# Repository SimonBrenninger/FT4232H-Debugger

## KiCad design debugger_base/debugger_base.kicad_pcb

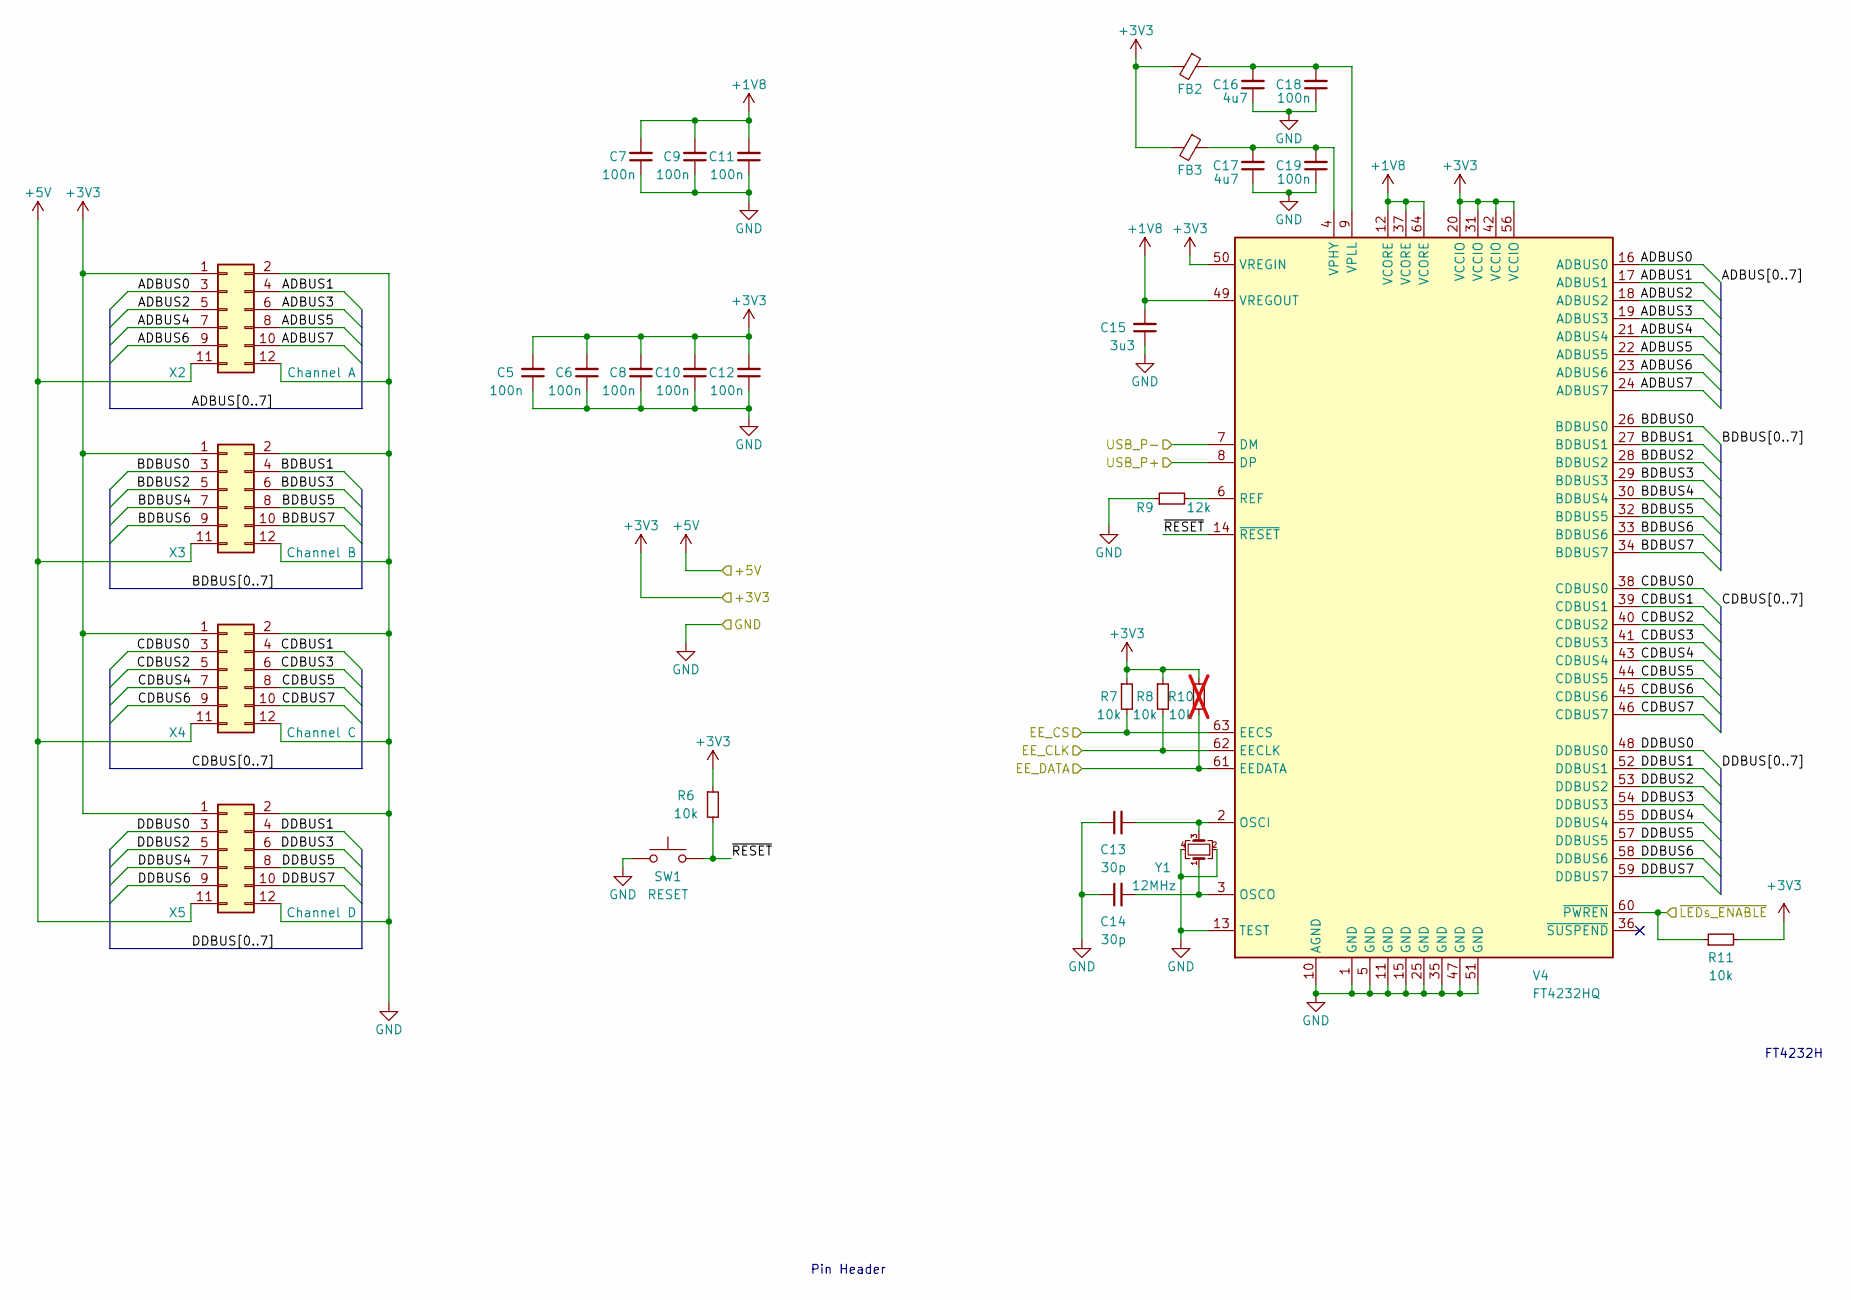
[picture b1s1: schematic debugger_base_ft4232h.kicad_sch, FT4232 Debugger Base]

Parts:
C5, C6, C7, C8, C9, C10, C11, C12, C18, C19: 100n; C_0402_1005Metric
C13, C14: 30p; C_0402_1005Metric
C15: 3u3; C_0402_1005Metric
C16, C17: 4u7; C_0402_1005Metric
FB2, FB3: FerriteBead_Small; L_0603_1608Metric
R6, R7, R8, R11: 10k; R_0402_1005Metric
R9: 12k; R_0402_1005Metric
R10: 10k; R_0402_1005Metric; not fitted
SW1: RESET; SW_SPST_EVQP2
V4: FT4232HQ; QFN-64-1EP_9x9mm_P0.5mm_EP4.35x4.35mm
X2: Channel A; header_female_02x06_613012243121
X3: Channel B; header_female_02x06_613012243121
X4: Channel C; header_female_02x06_613012243121
X5: Channel D; header_female_02x06_613012243121
Y1: 12MHz; Crystal_SMD_3225-4Pin_3.2x2.5mm

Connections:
+1V8: C7.2, C9.2, C11.2, C15.2, V4.12 (VCORE), V4.37 (VCORE), V4.49 (VREGOUT), V4.64 (VCORE)
+3V3: C5.2, C6.2, C8.2, C10.2, C12.2, FB2.2, FB3.2, R6.1, R7.1, R8.1, R10.1, R11.2, V4.20 (VCCIO), V4.31 (VCCIO), V4.42 (VCCIO), V4.50 (VREGIN), V4.56 (VCCIO), X2.1, X3.1, X4.1, X5.1; also elsewhere on the board
+5V: X2.11, X3.11, X4.11, X5.11; also elsewhere on the board
/FT4232H/ADBUS0: V4.16 (ADBUS0), X2.3
/FT4232H/ADBUS1: V4.17 (ADBUS1), X2.4
/FT4232H/ADBUS2: V4.18 (ADBUS2), X2.5
/FT4232H/ADBUS3: V4.19 (ADBUS3), X2.6
/FT4232H/ADBUS4: V4.21 (ADBUS4), X2.7
/FT4232H/ADBUS5: V4.22 (ADBUS5), X2.8
/FT4232H/ADBUS6: V4.23 (ADBUS6), X2.9
/FT4232H/ADBUS7: V4.24 (ADBUS7), X2.10
/FT4232H/BDBUS0: V4.26 (BDBUS0), X3.3
/FT4232H/BDBUS1: V4.27 (BDBUS1), X3.4
/FT4232H/BDBUS2: V4.28 (BDBUS2), X3.5
/FT4232H/BDBUS3: V4.29 (BDBUS3), X3.6
/FT4232H/BDBUS4: V4.30 (BDBUS4), X3.7
/FT4232H/BDBUS5: V4.32 (BDBUS5), X3.8
/FT4232H/BDBUS6: V4.33 (BDBUS6), X3.9
/FT4232H/BDBUS7: V4.34 (BDBUS7), X3.10
/FT4232H/CDBUS0: V4.38 (CDBUS0), X4.3
/FT4232H/CDBUS1: V4.39 (CDBUS1), X4.4
/FT4232H/CDBUS2: V4.40 (CDBUS2), X4.5
/FT4232H/CDBUS3: V4.41 (CDBUS3), X4.6
/FT4232H/CDBUS4: V4.43 (CDBUS4), X4.7
/FT4232H/CDBUS5: V4.44 (CDBUS5), X4.8
/FT4232H/CDBUS6: V4.45 (CDBUS6), X4.9
/FT4232H/CDBUS7: V4.46 (CDBUS7), X4.10
/FT4232H/DDBUS0: V4.48 (DDBUS0), X5.3
/FT4232H/DDBUS1: V4.52 (DDBUS1), X5.4
/FT4232H/DDBUS2: V4.53 (DDBUS2), X5.5
/FT4232H/DDBUS3: V4.54 (DDBUS3), X5.6
/FT4232H/DDBUS4: V4.55 (DDBUS4), X5.7
/FT4232H/DDBUS5: V4.57 (DDBUS5), X5.8
/FT4232H/DDBUS6: V4.58 (DDBUS6), X5.9
/FT4232H/DDBUS7: V4.59 (DDBUS7), X5.10
/FT4232H/EE_CLK: R8.2, V4.62 (EECLK); also elsewhere on the board
/FT4232H/EE_CS: R7.2, V4.63 (EECS); also elsewhere on the board
/FT4232H/EE_DATA: R10.2, V4.61 (EEDATA); also elsewhere on the board
/FT4232H/USB_P+: V4.8 (DP); also elsewhere on the board
/FT4232H/USB_P-: V4.7 (DM); also elsewhere on the board
/FT4232H/~LEDs_ENABLE: R11.1, V4.60 (~PWREN); also elsewhere on the board
/FT4232H/~RESET: R6.2, SW1.2, V4.14 (~RESET)
GND: C5.1, C6.1, C7.1, C8.1, C9.1, C10.1, C11.1, C12.1, C13.1, C14.1, C15.1, C16.1, C17.1, C18.1, C19.1, R9.1, SW1.1, V4.1 (GND), V4.5 (GND), V4.10 (AGND), V4.11 (GND), V4.13 (TEST), V4.15 (GND), V4.25 (GND), V4.35 (GND), V4.47 (GND), V4.51 (GND), X2.2, X2.12, X3.2, X3.12, X4.2, X4.12, X5.2, X5.12, Y1.2, Y1.4; also elsewhere on the board
unnamed: C13.2, V4.2 (OSCI), Y1.3
unnamed: C14.2, V4.3 (OSCO), Y1.1
unnamed: R9.2, V4.6 (REF)
unnamed: C17.2, C19.2, FB3.1, V4.4 (VPHY)
unnamed: C16.2, C18.2, FB2.1, V4.9 (VPLL)

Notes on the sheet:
FT4232H
Pin Header

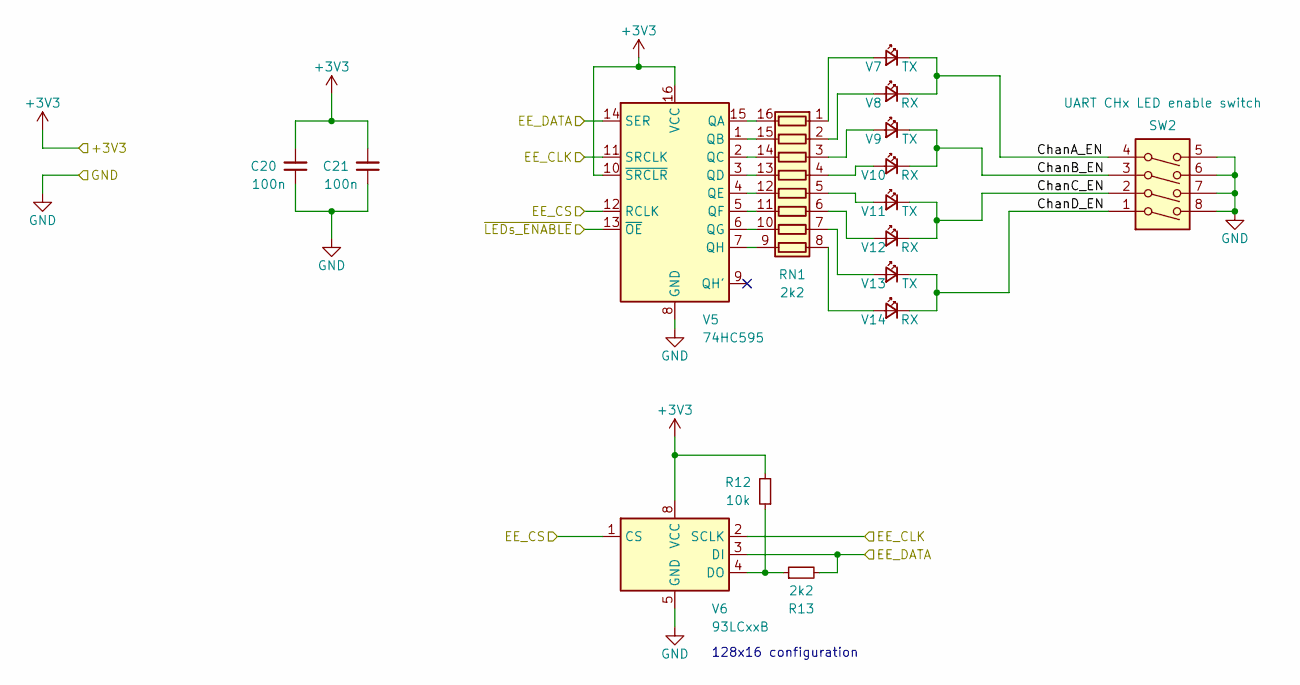
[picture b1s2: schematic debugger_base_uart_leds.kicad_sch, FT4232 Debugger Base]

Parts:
C20, C21: 100n; C_0402_1005Metric
R12: 10k; R_0402_1005Metric
R13: 2k2; R_0402_1005Metric
RN1: 2k2; R_Array_Convex_8x0602
SW2: UART CHx LED enable switch; SW_DIP_SPSTx04_Slide_6.7x11.72mm_W8.61mm_P2.54mm_LowProfile
V5: 74HC595
V6: 93LCxxB; DFN-8-1EP_3x2mm_P0.5mm_EP1.7x1.4mm
V7, V9, V11, V13: TX; LED_0603_1608Metric
V8, V10, V12, V14: RX; LED_0603_1608Metric

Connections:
+3V3: C20.2, C21.2, R12.2, V5.10 (~SRCLR), V5.16 (VCC), V6.8 (VCC); also elsewhere on the board
/FT4232H/EE_CLK: V5.11 (SRCLK), V6.2 (SCLK); also elsewhere on the board
/FT4232H/EE_CS: V5.12 (RCLK), V6.1 (CS); also elsewhere on the board
/FT4232H/EE_DATA: R13.2, V5.14 (SER), V6.3 (DI); also elsewhere on the board
/FT4232H/~LEDs_ENABLE: V5.13 (~OE); also elsewhere on the board
/LEDs, EEPROM/ChanA_EN: SW2.4, V7.1 (K), V8.1 (K)
/LEDs, EEPROM/ChanB_EN: SW2.3, V9.1 (K), V10.1 (K)
/LEDs, EEPROM/ChanC_EN: SW2.2, V11.1 (K), V12.1 (K)
/LEDs, EEPROM/ChanD_EN: SW2.1, V13.1 (K), V14.1 (K)
GND: C20.1, C21.1, SW2.5, SW2.6, SW2.7, SW2.8, V5.8 (GND), V6.5 (GND); also elsewhere on the board
unnamed: RN1.1 (R1.1), V7.2 (A)
unnamed: RN1.16 (R1.2), V5.15 (QA)
unnamed: RN1.2 (R2.1), V8.2 (A)
unnamed: RN1.15 (R2.2), V5.1 (QB)
unnamed: RN1.3 (R3.1), V9.2 (A)
unnamed: RN1.14 (R3.2), V5.2 (QC)
unnamed: RN1.4 (R4.1), V10.2 (A)
unnamed: RN1.13 (R4.2), V5.3 (QD)
unnamed: RN1.5 (R5.1), V11.2 (A)
unnamed: RN1.12 (R5.2), V5.4 (QE)
unnamed: RN1.6 (R6.1), V12.2 (A)
unnamed: RN1.11 (R6.2), V5.5 (QF)
unnamed: RN1.7 (R7.1), V13.2 (A)
unnamed: RN1.10 (R7.2), V5.6 (QG)
unnamed: RN1.8 (R8.1), V14.2 (A)
unnamed: RN1.9 (R8.2), V5.7 (QH)
unnamed: R12.1, R13.1, V6.4 (DO)

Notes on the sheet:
128x16 configuration

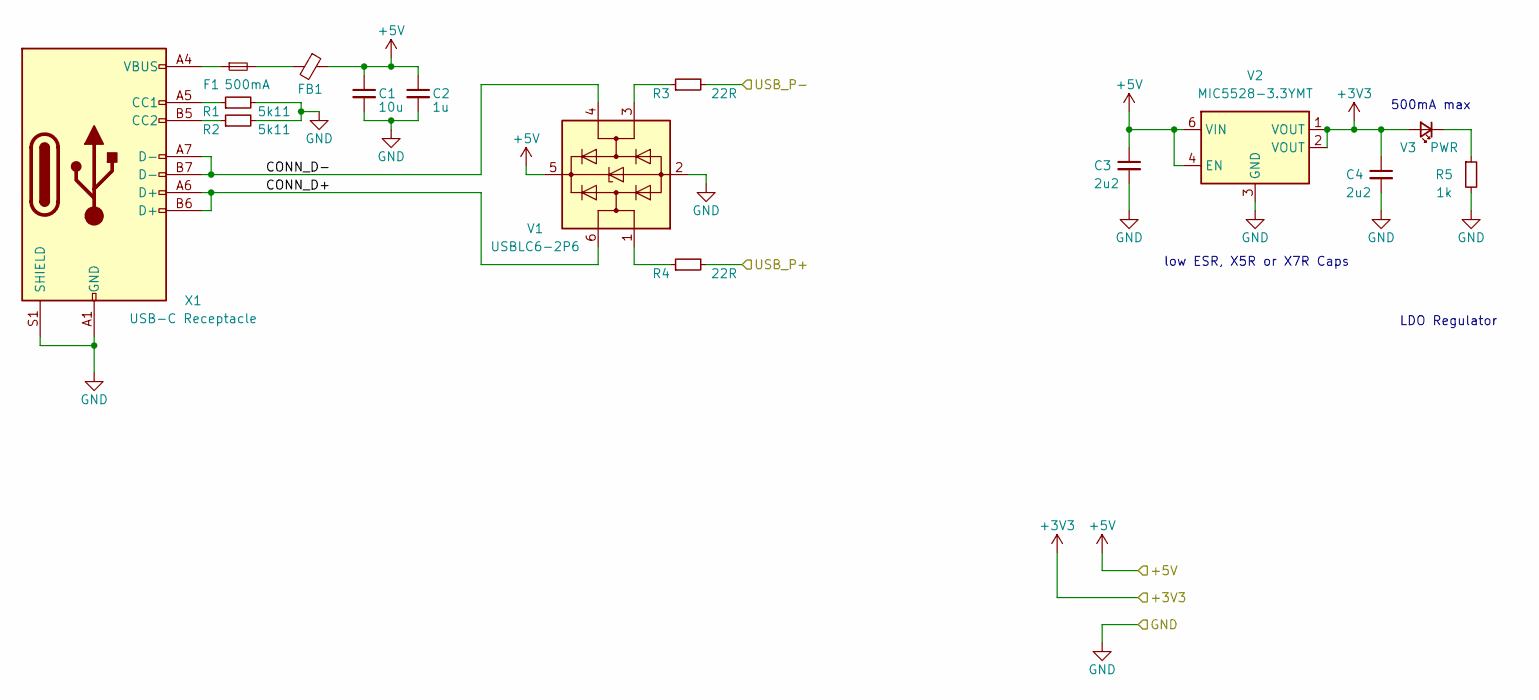
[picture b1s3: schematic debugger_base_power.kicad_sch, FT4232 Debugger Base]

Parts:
C1: 10u; C_0402_1005Metric
C2: 1u; C_0402_1005Metric
C3, C4: 2u2; C_0402_1005Metric
F1: 500mA; Fuse_0805_2012Metric
FB1: FerriteBead_Small; L_0603_1608Metric
R1, R2: 5k11; R_0402_1005Metric
R3, R4: 22R; R_0402_1005Metric
R5: 1k; R_0402_1005Metric
V1: USBLC6-2P6; SOT-666
V2: MIC5528-3.3YMT; DFN-6-1EP_1.2x1.2mm_P0.4mm_EP0.3x0.94mm_PullBack
V3: PWR; LED_0603_1608Metric
X1: USB-C Receptacle; USB_C_Receptacle_G-Switch_GT-USB-7010ASV

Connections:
+3V3: C4.1, V2.1 (VOUT), V2.2 (VOUT), V3.2 (A); also elsewhere on the board
+5V: C1.1, C2.1, C3.1, FB1.1, V1.5 (VBUS), V2.4 (EN), V2.6 (VIN); also elsewhere on the board
/FT4232H/USB_P+: R4.2; also elsewhere on the board
/FT4232H/USB_P-: R3.2; also elsewhere on the board
/Power/CONN_D+: V1.6 (I/O1), X1.A6 (D+), X1.B6 (D+)
/Power/CONN_D-: V1.4 (I/O2), X1.A7 (D-), X1.B7 (D-)
GND: C1.2, C2.2, C3.2, C4.2, R1.2, R2.2, R5.2, V1.2 (GND), V2.3 (GND), V2.7 (GND), X1.A1 (GND), X1.A12 (GND), X1.B1 (GND), X1.B12 (GND), X1.S1 (SHIELD); also elsewhere on the board
unnamed: F1.1, X1.A4 (VBUS), X1.A9 (VBUS), X1.B4 (VBUS), X1.B9 (VBUS)
unnamed: F1.2, FB1.2
unnamed: R3.1, V1.3 (I/O2)
unnamed: R4.1, V1.1 (I/O1)
unnamed: R5.1, V3.1 (K)
unnamed: R1.1, X1.A5 (CC1)
unnamed: R2.1, X1.B5 (CC2)

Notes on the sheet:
LDO Regulator
low ESR, X5R or X7R Caps
500mA max

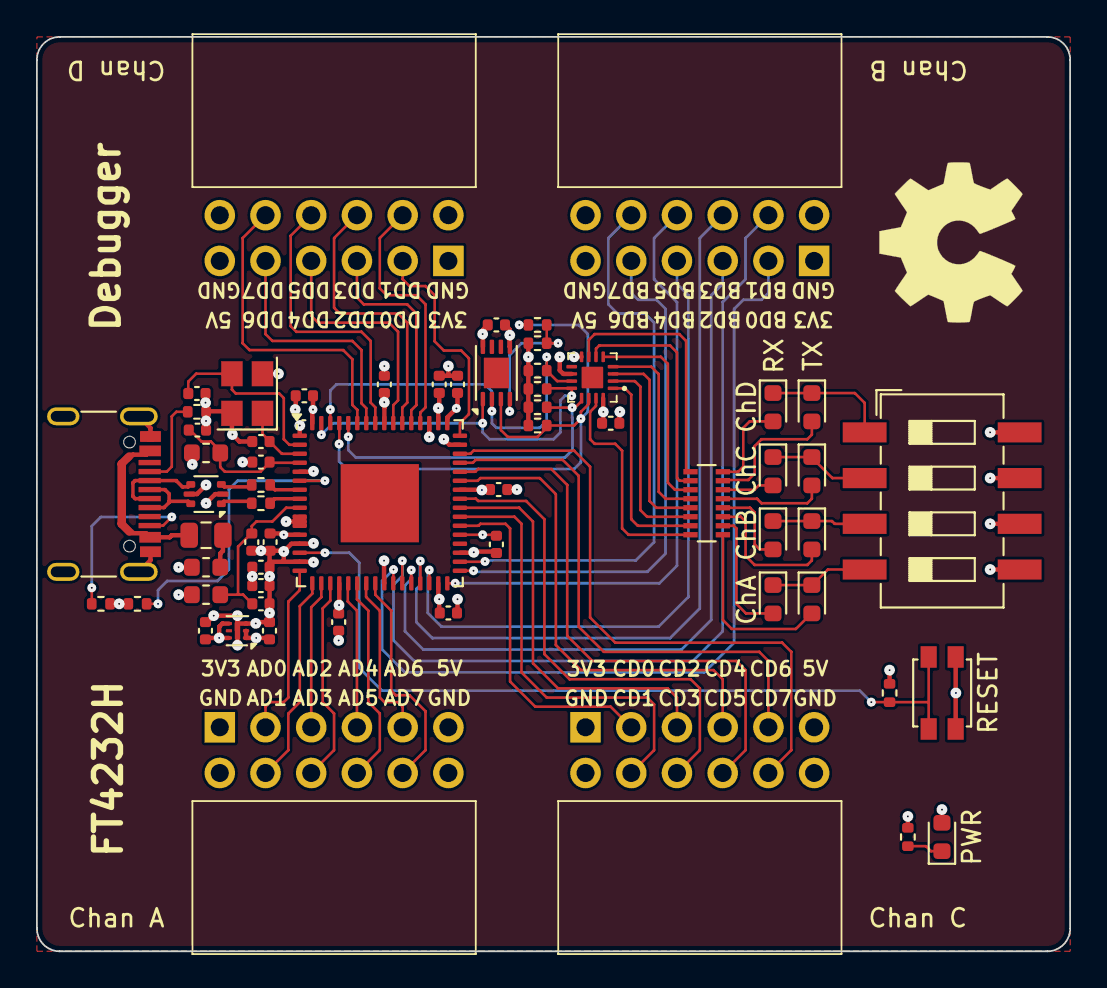
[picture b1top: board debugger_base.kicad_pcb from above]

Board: 4 copper layers, 57.4 x 50.8 mm, 61 parts (0 on the bottom side), 78 nets.

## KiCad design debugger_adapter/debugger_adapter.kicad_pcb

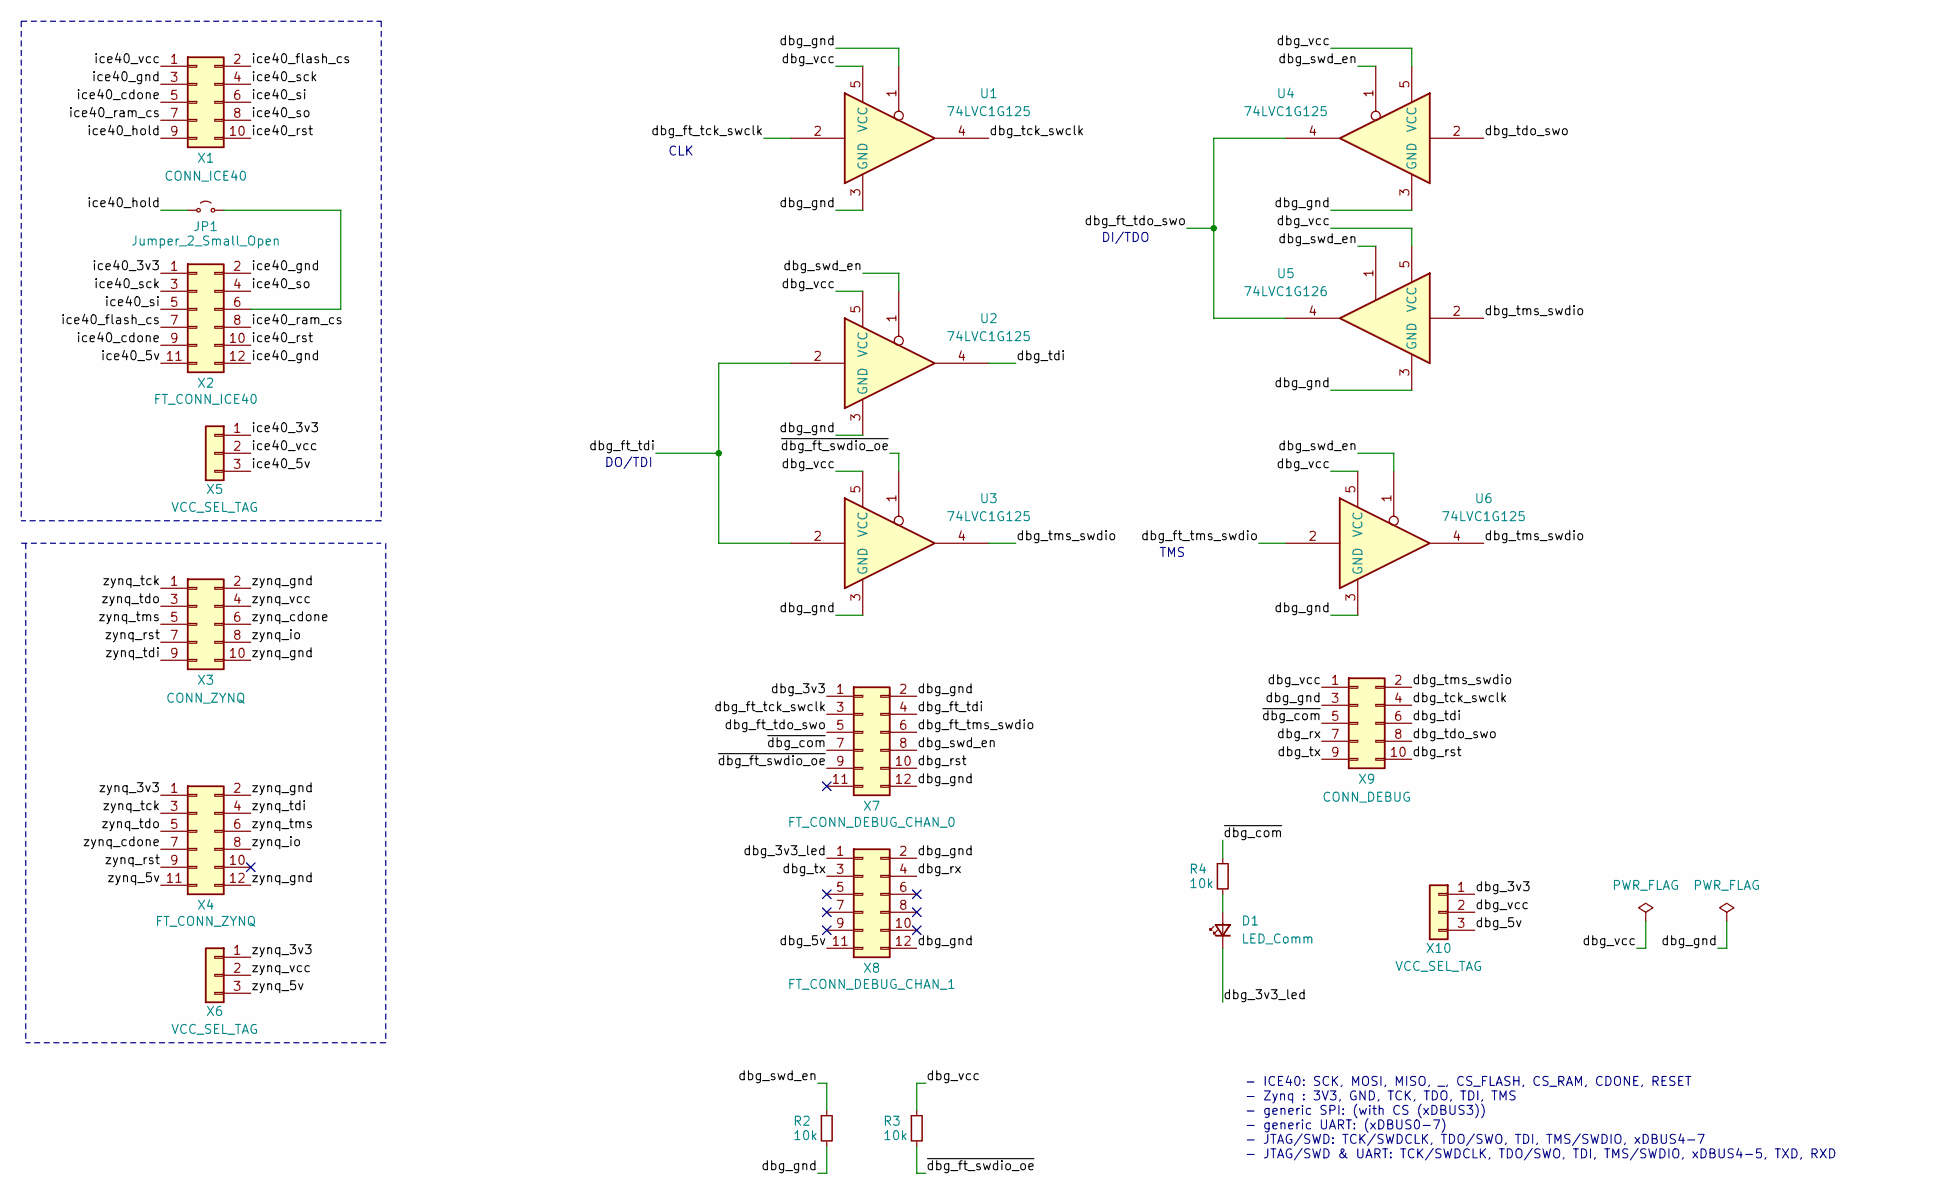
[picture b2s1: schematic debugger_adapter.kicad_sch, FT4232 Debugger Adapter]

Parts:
D1: LED_Comm; LED_0603_1608Metric
JP1: Jumper_2_Small_Open; PinHeader_1x02_P2.54mm_Vertical
R2, R3, R4: 10k; R_0402_1005Metric
U1, U2, U3, U4, U6: 74LVC1G125; SOT-353_SC-70-5
U5: 74LVC1G126; SOT-353_SC-70-5
X1: CONN_ICE40; IDC-Header_2x05_P2.54mm_Vertical
X2: FT_CONN_ICE40; header_male_02x06_HDRRA12W67P254_2X6_1524X254X503P
X3: CONN_ZYNQ; IDC-Header_2x05_P2.54mm_Vertical
X4: FT_CONN_ZYNQ; header_male_02x06_HDRRA12W67P254_2X6_1524X254X503P
X5, X6, X10: VCC_SEL_TAG; PinHeader_1x03_P2.54mm_Vertical
X7: FT_CONN_DEBUG_CHAN_0; header_male_02x06_HDRRA12W67P254_2X6_1524X254X503P
X8: FT_CONN_DEBUG_CHAN_1; header_male_02x06_HDRRA12W67P254_2X6_1524X254X503P
X9: CONN_DEBUG; IDC-Header_2x05_P2.54mm_Vertical

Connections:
/dbg_3v3: X7.1, X10.1
/dbg_3v3_led: D1.1 (K), X8.1
/dbg_5v: X8.11, X10.3
/dbg_ft_tck_swclk: U1.2, X7.3
/dbg_ft_tdi: U2.2, U3.2, X7.4
/dbg_ft_tdo_swo: U4.4, U5.4, X7.5
/dbg_ft_tms_swdio: U6.2, X7.6
/dbg_gnd: R2.2, U1.1, U1.3 (GND), U2.3 (GND), U3.3 (GND), U4.3 (GND), U5.3 (GND), U6.3 (GND), X7.2, X7.12, X8.2, X8.12, X9.3
/dbg_rst: X7.10, X9.10
/dbg_rx: X8.4, X9.7
/dbg_swd_en: R2.1, U2.1, U4.1, U5.1, U6.1, X7.8
/dbg_tck_swclk: U1.4, X9.4
/dbg_tdi: U2.4, X9.6
/dbg_tdo_swo: U4.2, X9.8
/dbg_tms_swdio: U3.4, U5.2, U6.4, X9.2
/dbg_tx: X8.3, X9.9
/dbg_vcc: R3.1, U1.5 (VCC), U2.5 (VCC), U3.5 (VCC), U4.5 (VCC), U5.5 (VCC), U6.5 (VCC), X9.1, X10.2
/ice40_3v3: X2.1, X5.1
/ice40_5v: X2.11, X5.3
/ice40_cdone: X1.5, X2.9
/ice40_flash_cs: X1.2, X2.7
/ice40_gnd: X1.3, X2.2, X2.12
/ice40_hold: JP1.1 (A), X1.9
/ice40_ram_cs: X1.7, X2.8
/ice40_rst: X1.10, X2.10
/ice40_sck: X1.4, X2.3
/ice40_si: X1.6, X2.5
/ice40_so: X1.8, X2.4
/ice40_vcc: X1.1, X5.2
/zynq_3v3: X4.1, X6.1
/zynq_5v: X4.11, X6.3
/zynq_cdone: X3.6, X4.7
/zynq_gnd: X3.2, X3.10, X4.2, X4.12
/zynq_io: X3.8, X4.8
/zynq_rst: X3.7, X4.9
/zynq_tck: X3.1, X4.3
/zynq_tdi: X3.9, X4.4
/zynq_tdo: X3.3, X4.5
/zynq_tms: X3.5, X4.6
/zynq_vcc: X3.4, X6.2
/~dbg_com: R4.1, X7.7, X9.5
/~dbg_ft_swdio_oe: R3.2, U3.1, X7.9
unnamed: D1.2 (A), R4.2
unnamed: JP1.2 (B), X2.6

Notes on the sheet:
CLK
- ICE40: SCK, MOSI, MISO, _, CS_FLASH, CS_RAM, CDONE, RESET - Zynq : 3V3, GND, TCK, TDO, TDI, TMS - generic SPI: (with CS (xDBUS3)) - generic UART: (xDBUS0-7) - JTAG/SWD: TCK/SWDCLK, TDO/SWO, TDI, TMS/SWDIO, xDBUS4-7 - JTAG/SWD & UART: TCK/SWDCLK, TDO/SWO, TDI, TMS/SWDIO, xDBUS4-5, TXD, RXD
DO/TDI
TMS
DI/TDO

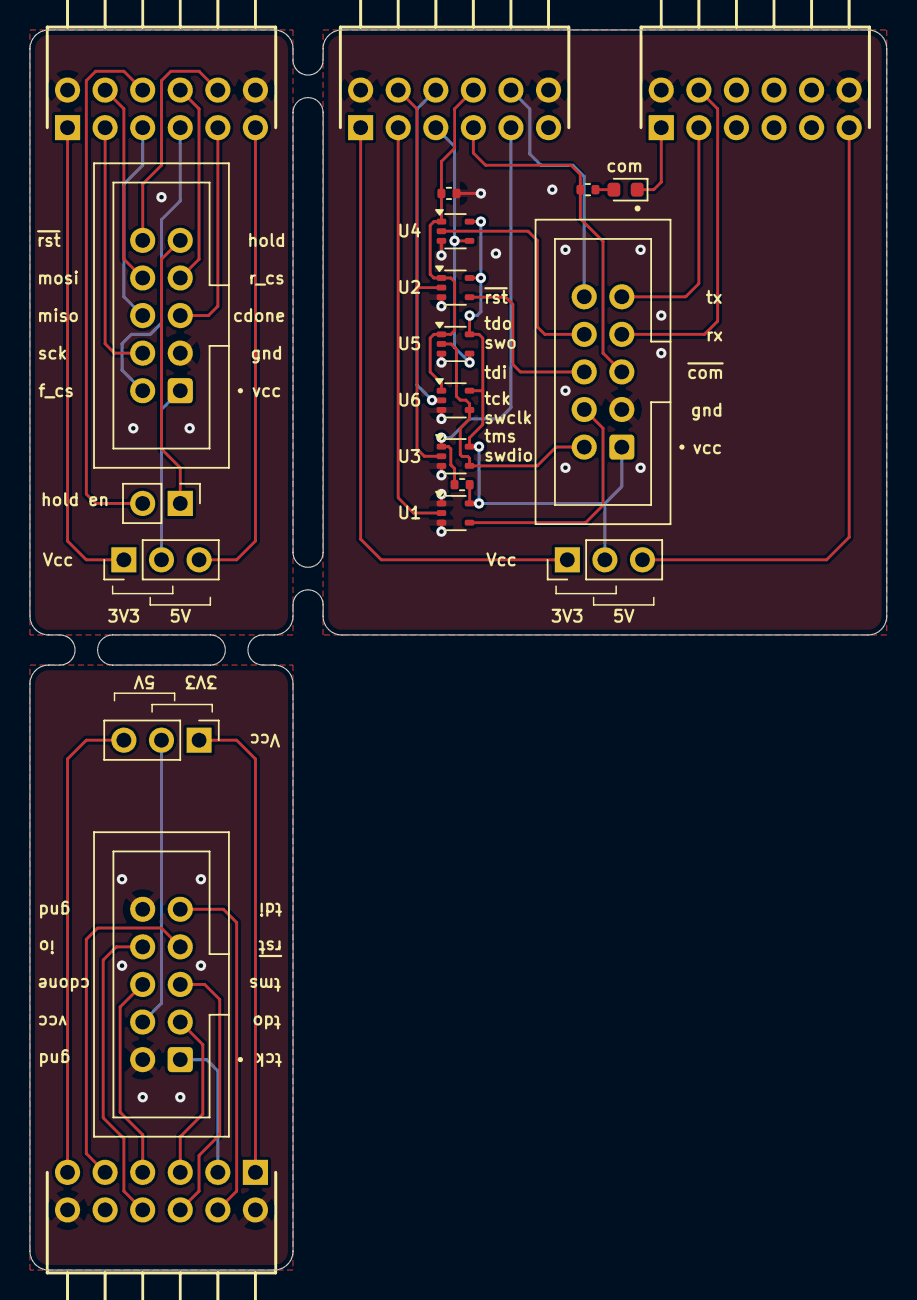
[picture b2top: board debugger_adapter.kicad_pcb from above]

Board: 2 copper layers, 57.9 x 83.8 mm, 21 parts (0 on the bottom side), 44 nets.

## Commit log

2024-02-11 add rx/tx status leds
2024-02-21 exclude traffic leds from base board
2024-03-16 add led dip-switches; create pcb
2024-04-20 finish base board pcb
2024-04-20 add docs and 3d models
2024-04-20 add adapter boards kicad project
2024-04-20 fix wrong silkscreen pinout
2024-06-02 add version number to silkscreen
2025-02-13 add design date
2025-02-14 remove unused footprint and 3d models
2025-02-14 decrease clearance of copper pours
